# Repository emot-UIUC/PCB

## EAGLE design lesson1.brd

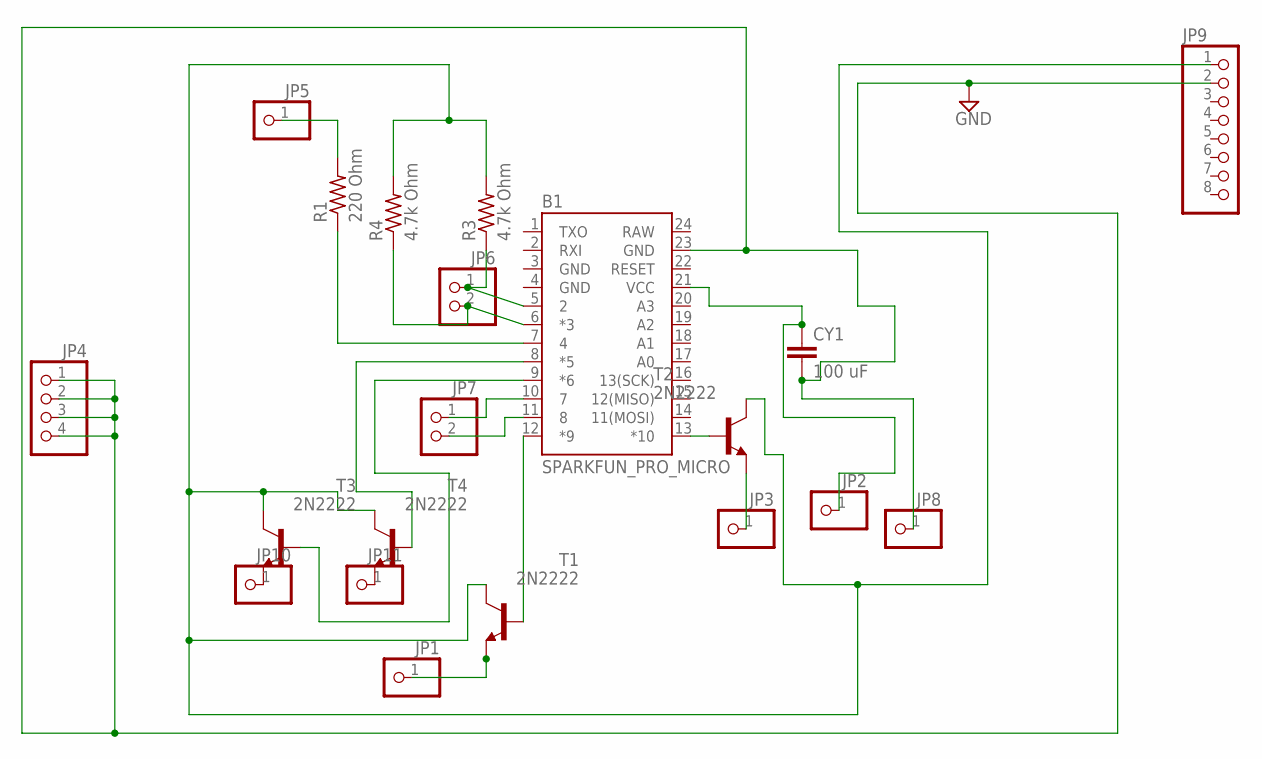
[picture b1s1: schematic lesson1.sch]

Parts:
B1: SPARKFUN_PRO_MICRO
CY1: 100 uF; YC7B5
JP1, JP2, JP3, JP5, JP8, JP10, JP11: PINHD-1X1; 1X01
JP4: PINHD-1X4; 1X04
JP6, JP7: PINHD-1X2; 1X02
JP9: PINHD-1X8; 1X08
R1: 220 Ohm; V526-0
R3, R4: 4.7k Ohm; V526-0
T1, T2, T3, T4: 2N2222; TO18

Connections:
GND: B1.3 (GND), B1.4 (GND), B1.23 (GND), CY1.2, JP4.1, JP4.2, JP4.3, JP4.4, JP8.1, JP9.2
unnamed: B1.13 (*10), T2.2 (B)
unnamed: B1.12 (*9), T1.2 (B)
unnamed: JP3.1, T2.1 (E)
unnamed: B1.10 (7), JP7.1
unnamed: JP5.1, R1.2
unnamed: JP1.1, T1.1 (E)
unnamed: B1.6 (*3), JP6.2, R4.1
unnamed: B1.7 (4), R1.1
unnamed: B1.11 (8), JP7.2
unnamed: B1.5 (2), JP6.1, R3.1
unnamed: JP11.1, T4.1 (E)
unnamed: B1.21 (VCC), CY1.1, JP2.1
unnamed: JP10.1, T3.1 (E)
unnamed: B1.9 (*6), T3.2 (B)
unnamed: JP9.1, R3.2, R4.2, T1.3 (C), T2.3 (C), T3.3 (C), T4.3 (C)
unnamed: B1.8 (*5), T4.2 (B)
RAW: B1.24 (RAW)

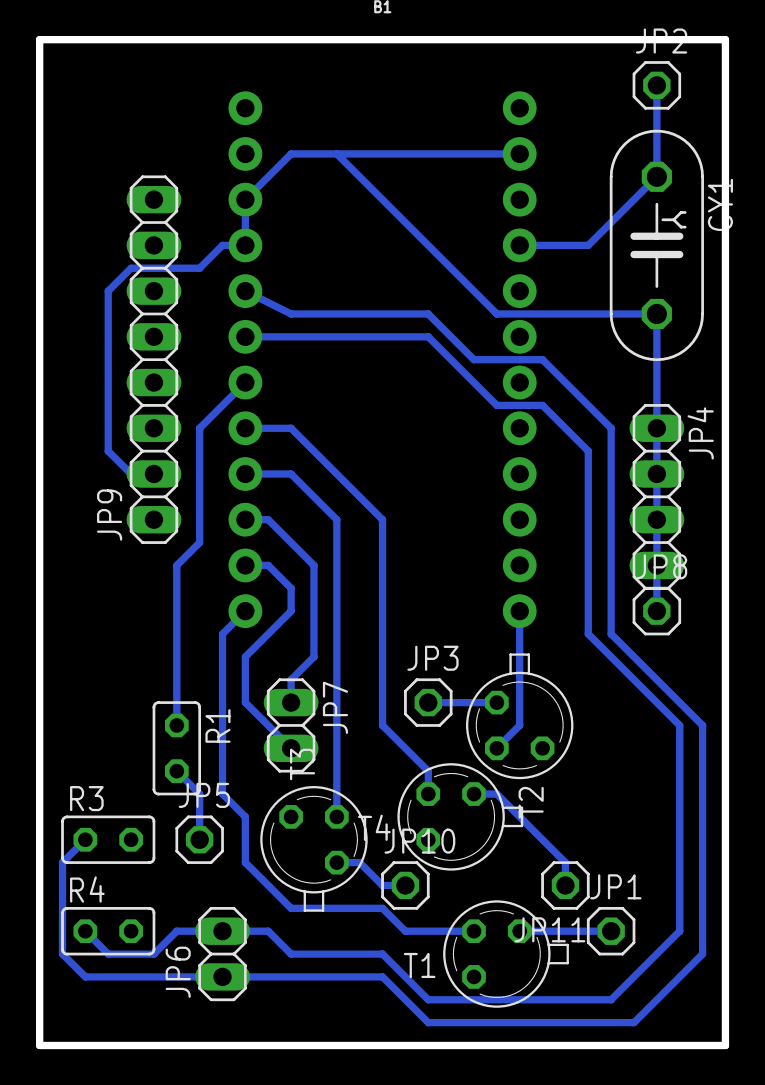
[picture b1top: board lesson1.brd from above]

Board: 2 copper layers, 38.1 x 55.9 mm, 20 parts (0 on the bottom side), 17 nets.

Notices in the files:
parts and their libraries:
SparkFun-Boards: Licensing: Creative Commons ShareAlike 4.0 International - https://creativecommons.org/licenses/by-sa/4.0
